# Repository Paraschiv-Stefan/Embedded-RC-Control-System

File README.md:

# Transmitter (Controller)

Custom handheld controller for wireless control of the RC vehicle.  
  
I took down a worn down Xbox one controller, reused any parts that I could and remade my own PCB that fits inside the controller case so i can have a similar feel to the racing games I used to play and enojoy.

---

##  Overview

This transmitter is built around a **custom 4-layer PCB**, this being my firts PCB design ever I find it easier to start with a 4 layers, but if I am to go back to designing I would only make it in 2 layers, the complexity of the PCB itself is too low to justify the 4 layers.

The goal of this controller was to transmitt data over a radio module HC-12 which works at 433Mhz, and is capable of transmitting at distances as far away as 1km

---

## Hardware Design

### Microcontroller

* **PIC16F15276**
  Handles input processing and communication with the receiver. Cheap and easy to programm being a chip supported in the MCC from MpLab X IDE with a lot of configurable pins.

---

### User Input

* **Dual Joysticks**
  Provides steering control and menu configuration on the receiver

* **Hall Effect Sensors (from Xbox One controller)**
  Used for **high-precision, contactless throttle control**, improving reliability and eliminating mechanical wear.

---

## 📐 Schematic

> The schematic is fairly simple, at the center of it being the microcontroller, and all the analog pins needed that go to the joysticks and hall effect sensors as well as the uart communication for the HC-12 module.
---

## PCB Design

* **4-layer PCB**
* Designed for:

  * Compact handheld form factor

---

## PCB Layers

### Layer 1

> The first layer is primarily concerned with power distribution, ensuring all components across the board receive their required supply voltages.

### Layer 2

> This layer is dominated by the ground plane, while also accommodating the analog signal traces associated with the joystick inputs.

### Layer 3

> Similarly to the second layer, this layer is largely devoted to the ground plane, reinforcing the overall grounding strategy of the board.
### Layer 4

> The final layer is comparatively sparse, carrying only the traces dedicated to UART communication — keeping this relatively noise-sensitive interface clean and uncluttered

---

## Firmware

The firmware is responsible for:

* Reading joystick and sensor inputs
* Processing control signals
* Transmitting data wirelessly to the receiver with the help of the HC-12 module

---

## Functionality

* Real-time throttle and steering control
* Smooth input response using Hall effect sensing
* Reliable wireless communication
* Response time can be improved

---

## Notes

* Designed specifically for RC applications
* Focus on precision and responsiveness
* Built using salvaged components (Xbox controller sensors)

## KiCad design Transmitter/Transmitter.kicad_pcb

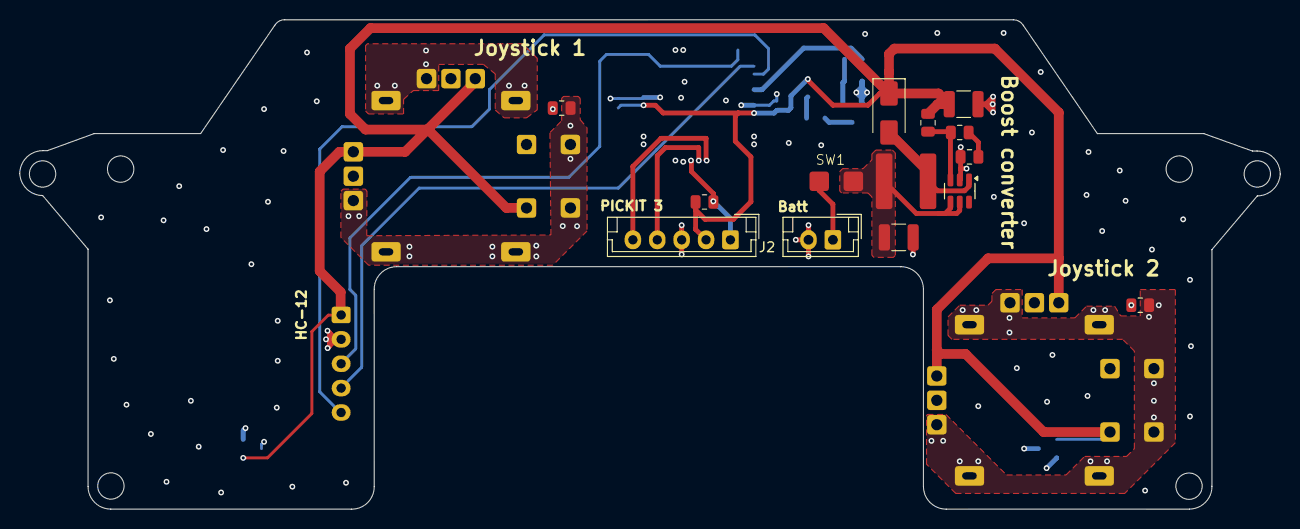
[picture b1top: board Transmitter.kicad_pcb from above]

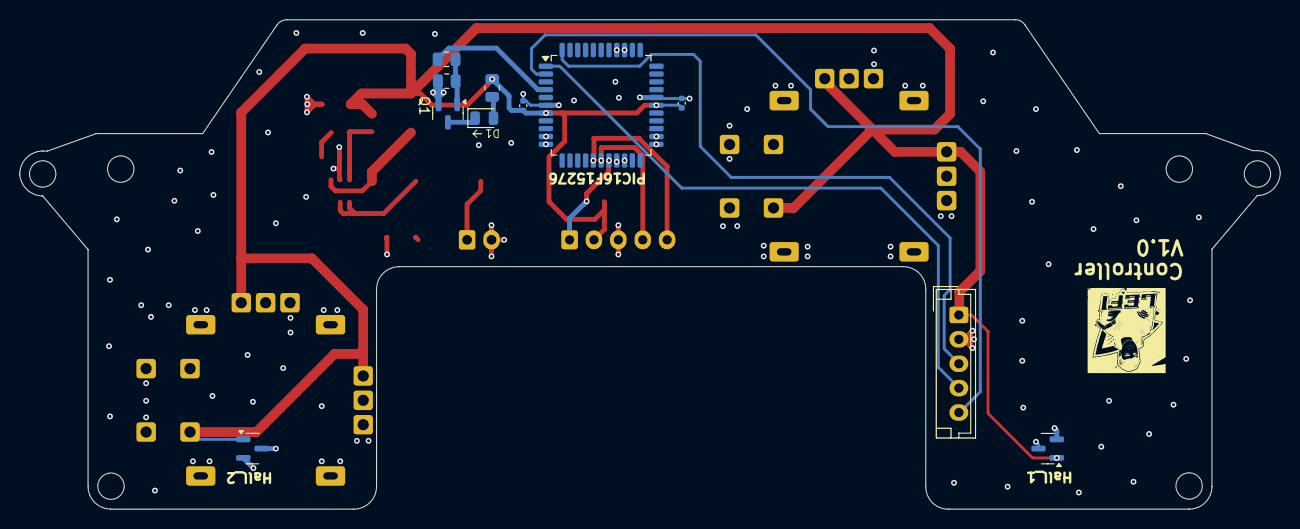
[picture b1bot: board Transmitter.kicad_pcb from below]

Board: 4 copper layers, 129.2 x 50.2 mm, 33 parts (11 on the bottom side), 25 nets.

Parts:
C1, C2: 100n; C_0402_1005Metric
C20, C21: 22u; C_1210_3225Metric
D1: LED; LED_0805_2012Metric
D20: SS14; D_SMA
H1, H2, H3, H4, H5, H6: MountingHole; MountingHole_2.7mm
J1, J4: Conn_01x05; JST_EH_B5B-EH-A_1x05_P2.50mm_Vertical
J2: Conn_01x02; JST_EH_B2B-EH-A_1x02_P2.50mm_Vertical
L20: 15u; inductor(mt3608)15u
Q1: BC817; SOT-23
R1, R22, R40, R41: 10k; R_0805_2012Metric
R20: 100; R_0805_2012Metric
R21, R31: 1k; R_0805_2012Metric
R30: 10.5k; R_0805_2012Metric
R32: 500; R_0805_2012Metric
SW1: SW_DIP_x01; Untitled
U1, U5: SOT-23
U2, U4: Joystick
U6: PIC18F4431-IPT; TQFP-44_10x10mm_P0.8mm
U20: MT3608; SOT-23-6

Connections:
/Hall_1: U1.2 (OUTPUT), U6.20 (RA1/AN1)
/Hall_2: U5.2 (OUTPUT), U6.19 (RA0/AN0)
/LED: R21.2, U6.4 (PWM6/RD6)
/MCLR: J4.1, R1.2, U6.18 (Vpp/~MCLR/RE3)
/PGC: J4.5, U6.16 (RB6/KBI2/PGC)
/PGD: J4.4, U6.17 (RB7/KBI3/PGD)
/RX: J1.4, U6.1 (RX/SDO/DT/RC7)
/SW1: R40.2, U2.3 (SW), U6.23 (RA4/AN4/CAP3/QEB)
/SW2: R41.2, U4.3 (SW), U6.24 (RA5/AN5/LVDIN)
/Set: J1.5, U6.2 (~FLTA/RD4)
/TX: J1.3, U6.44 (TX/~SS/CK/RC6)
/VBAT: C20.1, L20.1, SW1.2, U20.4 (EN), U20.5 (IN)
/VDD: C1.1, C2.1, C21.1, D20.1 (K), J1.1, J4.2, R1.1, R20.1, R30.1, U1.1 (VCC), U2.1 (VCC), U2.6 (SW), U4.1 (VCC), U4.6 (SW), U5.1 (VCC), U6.7 (VDD), U6.28 (AVDD)
/X1: U2.4 (Rx), U6.36 (~FLTB/CCP1/RC2)
/X2: U4.4 (Rx), U6.10 (RB2/PWM2)
/Y1: U2.5 (Ry), U6.37 (INT0/T5CKI/T0CKI/RC3)
/Y2: U4.5 (Ry), U6.11 (RB3/PWM3)
GND: C1.2, C2.2, C20.2, C21.2, J1.2, J2.2, J4.3, Q1.2 (E), R22.2, R32.2, R40.1, R41.1, U1.3 (GND), U2.0 (GND), U4.0 (GND), U5.3 (GND), U6.6 (VSS), U6.29 (AVSS), U20.2 (GND)
unnamed: D1.2 (A), R20.2
unnamed: D1.1 (K), Q1.3 (C)
unnamed: D20.2 (A), L20.2, U20.1 (SW)
unnamed: J2.1, SW1.1
unnamed: Q1.1 (B), R21.1, R22.1
unnamed: R31.2, R32.1
unnamed: R30.2, R31.1, U20.3 (FB)

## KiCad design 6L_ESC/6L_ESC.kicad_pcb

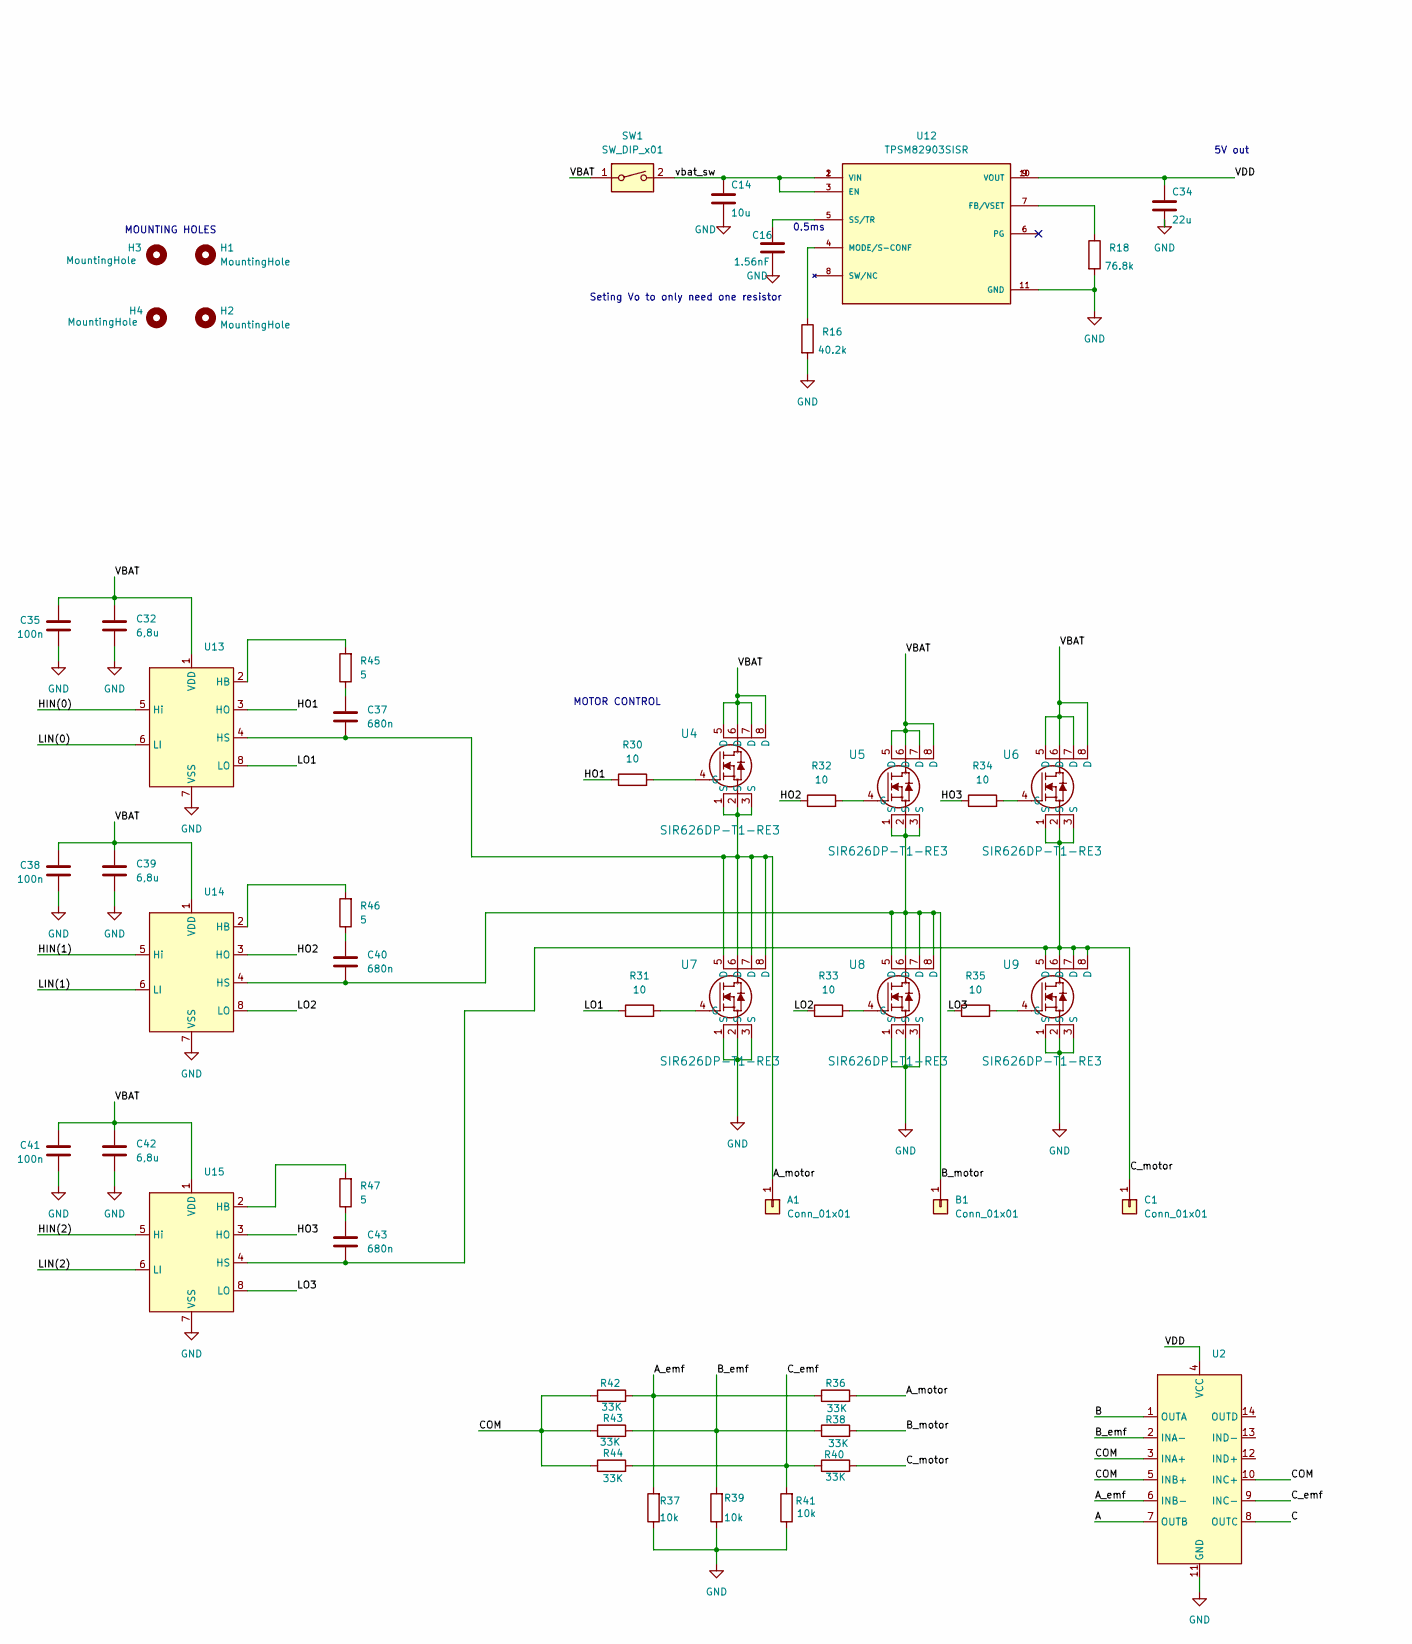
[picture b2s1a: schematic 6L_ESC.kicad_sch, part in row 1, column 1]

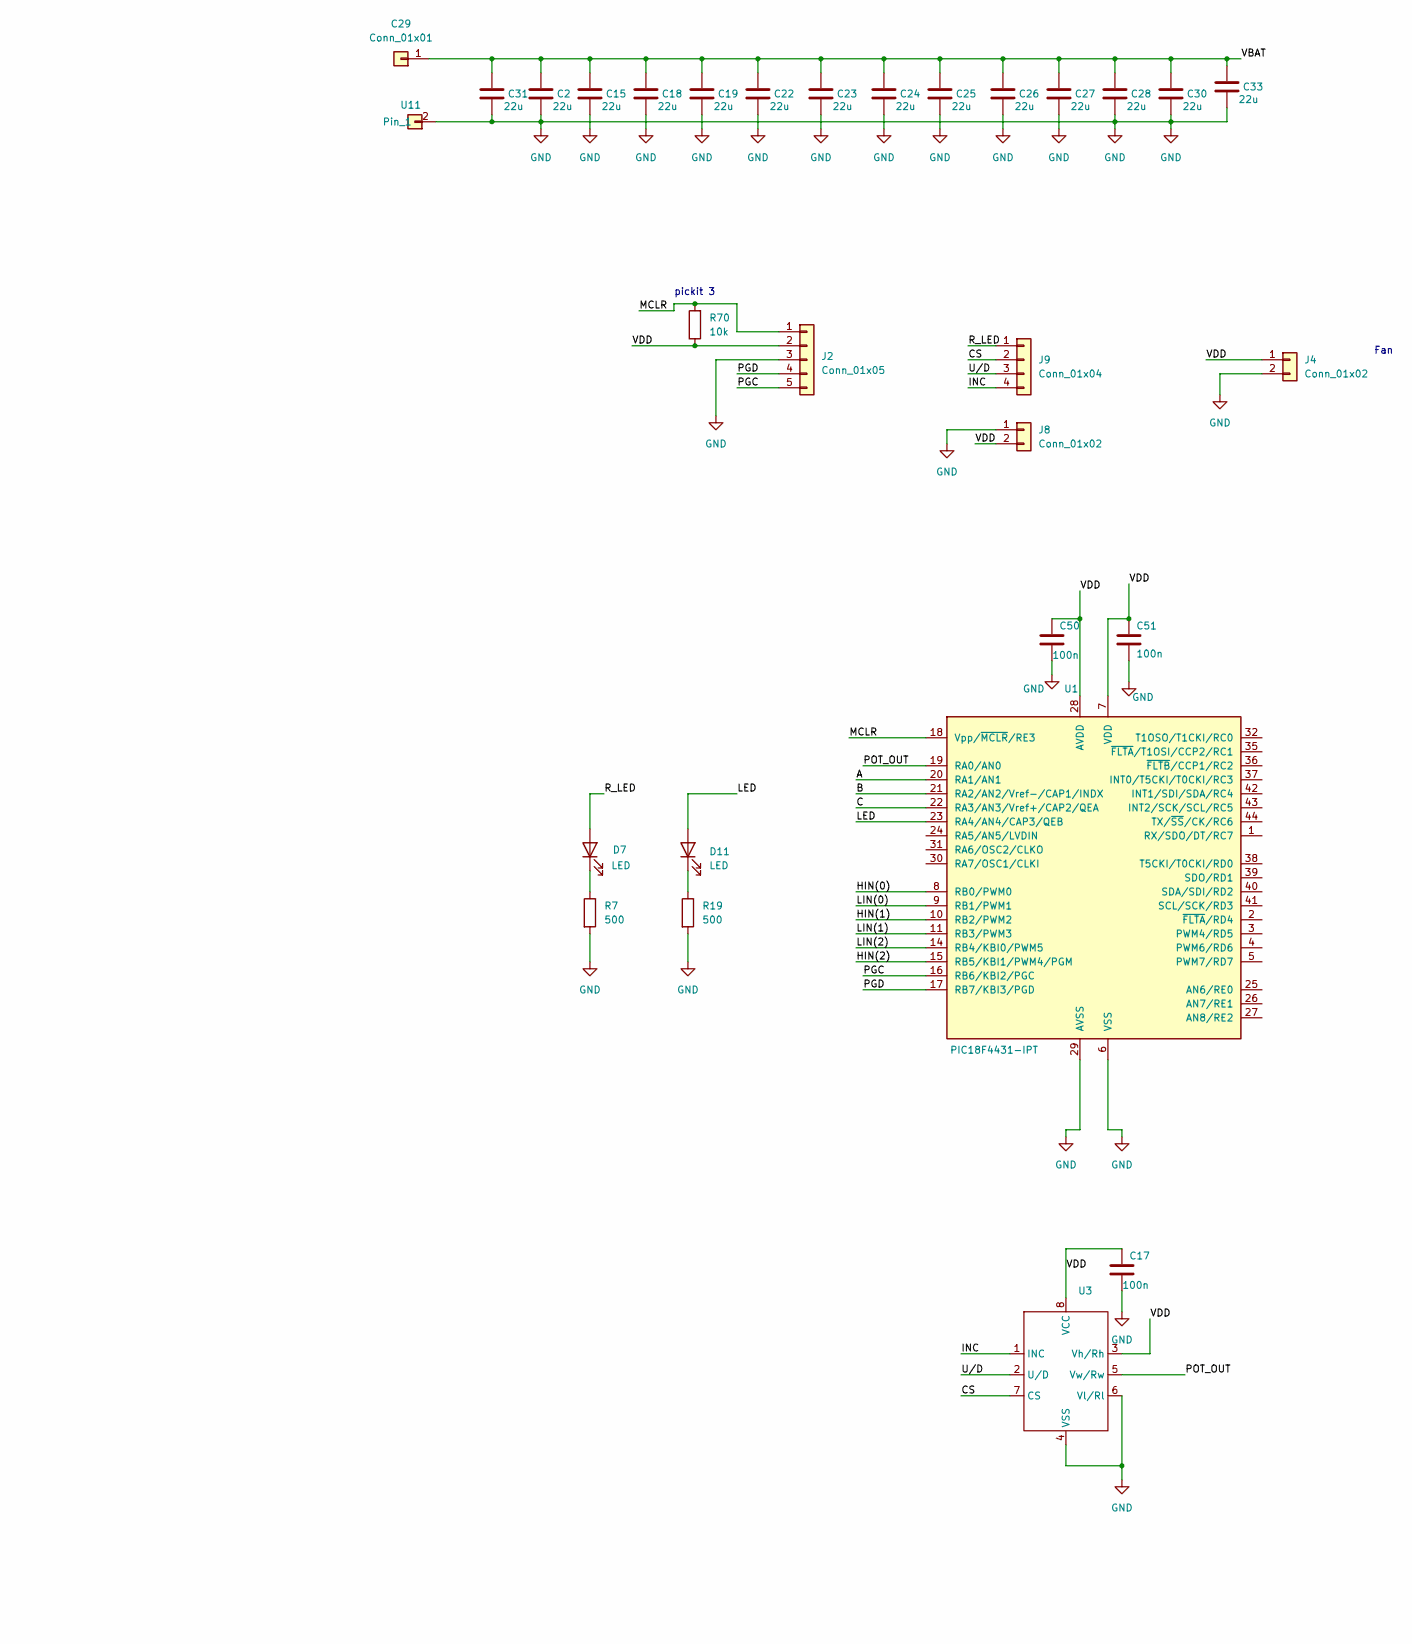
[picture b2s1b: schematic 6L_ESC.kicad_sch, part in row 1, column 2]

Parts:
A1: Conn_01x01; PHASE_PAD
B1: Conn_01x01; PHASE_PAD
C1: Conn_01x01; PHASE_PAD
C2, C15, C18, C19, C22, C23, C24, C25, C26, C27, C28, C30, C31, C33, C34: 22u; C_1210_3225Metric
C14: 10u; C_0805_2012Metric
C16: 1.56nF; C_0603_1608Metric
C17, C50, C51: 100n; C_0402_1005Metric
C29: Conn_01x01; BAT+
C32, C39, C42: 6,8u; C_0603_1608Metric
C35, C38, C41: 100n; C_0603_1608Metric
C37, C40, C43: 680n; C_0603_1608Metric
D7, D11: LED; LED_0805_2012Metric
H1, H2, H3, H4: MountingHole; MountingHole_2.1mm
J2: Conn_01x05; JST_EH_B5B-EH-A_1x05_P2.50mm_Vertical
J4: Conn_01x02; JST_EH_B2B-EH-A_1x02_P2.50mm_Vertical
J8: Conn_01x02; PinHeader_1x02_P2.54mm_Vertical
J9: Conn_01x04; PinHeader_1x04_P2.54mm_Vertical
R7, R19: 500; R_0805_2012Metric
R16: 40.2k; R_0603_1608Metric
R18: 76.8k; R_0603_1608Metric
R30, R31, R32, R33, R34, R35: 10; R_0805_2012Metric
R36, R38, R40, R42, R43, R44: 33K; R_0805_2012Metric
R37, R39, R41, R70: 10k; R_0805_2012Metric
R45, R46, R47: 5; R_1206_3216Metric
SW1: SW_DIP_x01; switch
U1: PIC18F4431-IPT; TQFP-44_10x10mm_P0.8mm
U2: comp_tssop-14_lm324
U3: SOIC-8_3.9x4.9mm_P1.27mm
U4, U5, U6: SIR626DP-T1-RE3; sir626_redefined
U7, U8, U9: SIR626DP-T1-RE3; sir626_les_holes
U11: BAT-
U12: TPSM82903SISR; IC_TPSM82903SISR; PARTREV B; DigiKey_Part_Number 296-TPSM82903SISRCT-ND
U13, U14, U15: NVC51511

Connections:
/A: U1.20 (RA1/AN1), U2.7 (OUTB)
/A_emf: R36.1, R37.2, R42.2, U2.6 (INB-)
/A_motor: A1.1, C37.2, R36.2, U4.1 (S), U4.2 (S), U4.3 (S), U7.5 (D), U7.6 (D), U7.7 (D), U7.8 (D), U13.4 (HS)
/B: U1.21 (RA2/AN2/Vref-/CAP1/INDX), U2.1 (OUTA)
/B_emf: R38.1, R39.2, R43.1, U2.2 (INA-)
/B_motor: B1.1, C40.2, R38.2, U5.1 (S), U5.2 (S), U5.3 (S), U8.5 (D), U8.6 (D), U8.7 (D), U8.8 (D), U14.4 (HS)
/C: U1.22 (RA3/AN3/Vref+/CAP2/QEA), U2.8 (OUTC)
/COM: R42.1, R43.2, R44.1, U2.3 (INA+), U2.5 (INB+), U2.10 (INC+)
/CS: J9.2, U3.7 (CS)
/C_emf: R40.1, R41.2, R44.2, U2.9 (INC-)
/C_motor: C1.1, C43.2, R40.2, U6.1 (S), U6.2 (S), U6.3 (S), U9.5 (D), U9.6 (D), U9.7 (D), U9.8 (D), U15.4 (HS)
/HIN(0): U1.8 (RB0/PWM0), U13.5 (Hi)
/HIN(1): U1.10 (RB2/PWM2), U14.5 (Hi)
/HIN(2): U1.15 (RB5/KBI1/PWM4/PGM), U15.5 (Hi)
/HO1: R30.1, U13.3 (HO)
/HO2: R32.1, U14.3 (HO)
/HO3: R34.1, U15.3 (HO)
/INC: J9.4, U3.1 (INC)
/LED: D11.2 (A), U1.23 (RA4/AN4/CAP3/QEB)
/LIN(0): U1.9 (RB1/PWM1), U13.6 (LI)
/LIN(1): U1.11 (RB3/PWM3), U14.6 (LI)
/LIN(2): U1.14 (RB4/KBI0/PWM5), U15.6 (LI)
/LO1: R31.1, U13.8 (LO)
/LO2: R33.1, U14.8 (LO)
/LO3: R35.1, U15.8 (LO)
/MCLR: J2.1, R70.2, U1.18 (Vpp/~MCLR/RE3)
/PGC: J2.5, U1.16 (RB6/KBI2/PGC)
/PGD: J2.4, U1.17 (RB7/KBI3/PGD)
/POT_OUT: U1.19 (RA0/AN0), U3.5 (Vw/Rw)
/R_LED: D7.2 (A), J9.1
/U/D: J9.3, U3.2 (U/D)
/VBAT: C2.1, C15.1, C18.1, C19.1, C22.1, C23.1, C24.1, C25.1, C26.1, C27.1, C28.1, C29.1, C30.1, C31.1, C32.1, C33.1, C35.1, C38.1, C39.1, C41.1, C42.1, SW1.1, U4.5 (D), U4.6 (D), U4.7 (D), U4.8 (D), U5.5 (D), U5.6 (D), U5.7 (D), U5.8 (D), U6.5 (D), U6.6 (D), U6.7 (D), U6.8 (D), U13.1 (VDD), U14.1 (VDD), U15.1 (VDD)
/VDD: C17.1, C34.1, C50.1, C51.1, J2.2, J4.1, J8.2, R70.1, U1.7 (VDD), U1.28 (AVDD), U2.4 (VCC), U3.3 (Vh/Rh), U3.8 (VCC), U12.9 (VOUT), U12.10 (VOUT)
/vbat_sw: C14.1, SW1.2, U12.1 (VIN), U12.2 (VIN), U12.3 (EN)
GND: C2.2, C14.2, C15.2, C16.2, C17.2, C18.2, C19.2, C22.2, C23.2, C24.2, C25.2, C26.2, C27.2, C28.2, C30.2, C31.2, C32.2, C33.2, C34.2, C35.2, C38.2, C39.2, C41.2, C42.2, C50.2, C51.2, J2.3, J4.2, J8.1, R7.2, R16.2, R18.2, R19.2, R37.1, R39.1, R41.1, U1.6 (VSS), U1.29 (AVSS), U2.11 (GND), U3.4 (VSS), U3.6 (Vl/Rl), U7.1 (S), U7.2 (S), U7.3 (S), U8.1 (S), U8.2 (S), U8.3 (S), U9.1 (S), U9.2 (S), U9.3 (S), U11.2 (Pin_1), U12.11 (GND), U13.7 (VSS), U14.7 (VSS), U15.7 (VSS)
unnamed: C37.1, R45.1
unnamed: C40.1, R46.1
unnamed: C43.1, R47.1
unnamed: D7.1 (K), R7.1
unnamed: D11.1 (K), R19.1
unnamed: R30.2, U4.4 (G)
unnamed: R32.2, U5.4 (G)
unnamed: R34.2, U6.4 (G)
unnamed: R31.2, U7.4 (G)
unnamed: R33.2, U8.4 (G)
unnamed: R35.2, U9.4 (G)
unnamed: R18.1, U12.7 (FB/VSET)
unnamed: R16.1, U12.4 (MODE/S-CONF)
unnamed: C16.1, U12.5 (SS/TR)
unnamed: R45.2, U13.2 (HB)
unnamed: R46.2, U14.2 (HB)
unnamed: R47.2, U15.2 (HB)

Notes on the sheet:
Seting Vo to only need one resistor
Fan
MOTOR CONTROL
MOUNTING HOLES
0.5ms
pickit 3
5V out

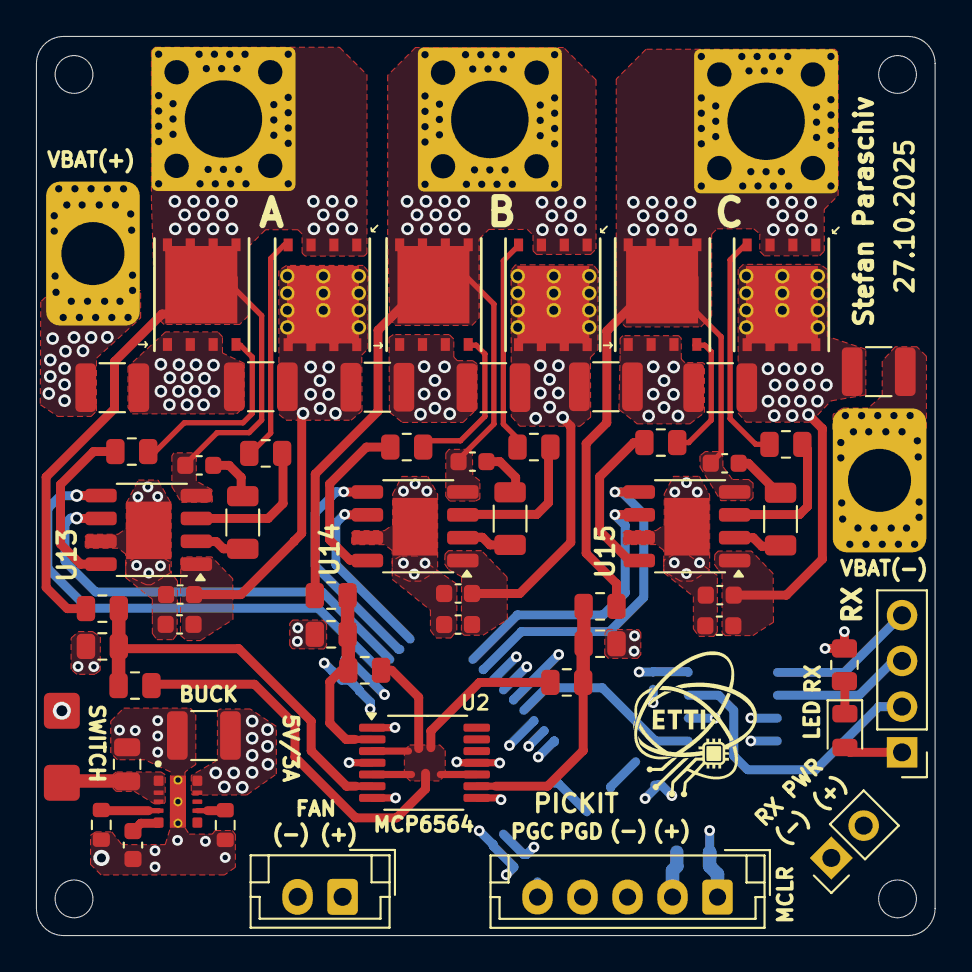
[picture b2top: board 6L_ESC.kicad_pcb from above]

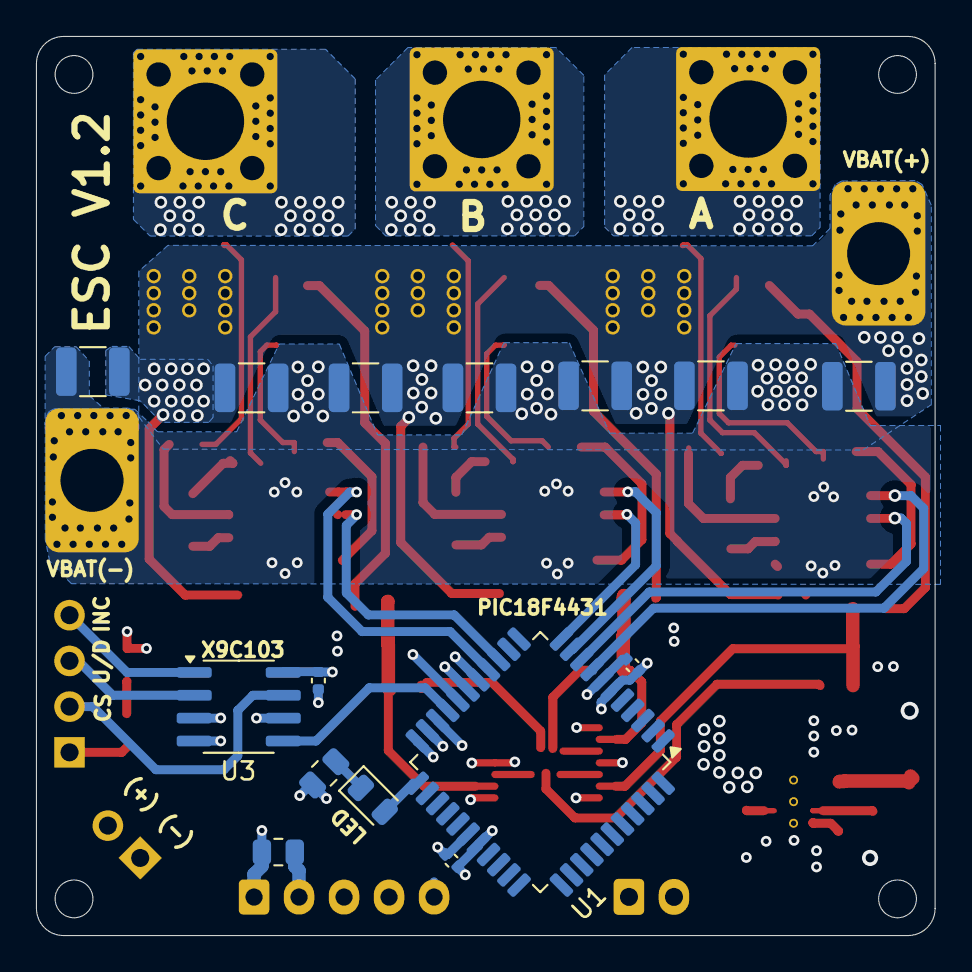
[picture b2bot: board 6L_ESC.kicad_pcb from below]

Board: 6 copper layers, 49.9 x 49.9 mm, 81 parts (15 on the bottom side), 52 nets.

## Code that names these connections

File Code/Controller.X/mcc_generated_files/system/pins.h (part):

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// get/set IO_RA0 aliases
#define IO_RA0_TRIS                 TRISAbits.TRISA0
#define IO_RA0_LAT                  LATAbits.LATA0
#define IO_RA0_PORT                 PORTAbits.RA0
#define IO_RA0_WPU                  WPUAbits.WPUA0
#define IO_RA0_OD                   ODCONAbits.ODCA0
#define IO_RA0_ANS                  ANSELAbits.ANSA0
#define IO_RA0_SetHigh()            do { LATAbits.LATA0 = 1; } while(0)
#define IO_RA0_SetLow()             do { LATAbits.LATA0 = 0; } while(0)
#define IO_RA0_Toggle()             do { LATAbits.LATA0 = ~LATAbits.LATA0; } while(0)
#define IO_RA0_GetValue()           PORTAbits.RA0
#define IO_RA0_SetDigitalInput()    do { TRISAbits.TRISA0 = 1; } while(0)
#define IO_RA0_SetDigitalOutput()   do { TRISAbits.TRISA0 = 0; } while(0)
#define IO_RA0_SetPullup()          do { WPUAbits.WPUA0 = 1; } while(0)
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// get/set IO_RA1 aliases
#define IO_RA1_TRIS                 TRISAbits.TRISA1
#define IO_RA1_LAT                  LATAbits.LATA1
#define IO_RA1_PORT                 PORTAbits.RA1
#define IO_RA1_WPU                  WPUAbits.WPUA1
#define IO_RA1_OD                   ODCONAbits.ODCA1
#define IO_RA1_ANS                  ANSELAbits.ANSA1
#define IO_RA1_SetHigh()            do { LATAbits.LATA1 = 1; } while(0)
#define IO_RA1_SetLow()             do { LATAbits.LATA1 = 0; } while(0)
#define IO_RA1_Toggle()             do { LATAbits.LATA1 = ~LATAbits.LATA1; } while(0)
#define IO_RA1_GetValue()           PORTAbits.RA1
#define IO_RA1_SetDigitalInput()    do { TRISAbits.TRISA1 = 1; } while(0)
#define IO_RA1_SetDigitalOutput()   do { TRISAbits.TRISA1 = 0; } while(0)
#define IO_RA1_SetPullup()          do { WPUAbits.WPUA1 = 1; } while(0)
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// get/set IO_RA2 aliases
#define IO_RA2_TRIS                 TRISAbits.TRISA2
#define IO_RA2_LAT                  LATAbits.LATA2
#define IO_RA2_PORT                 PORTAbits.RA2
#define IO_RA2_WPU                  WPUAbits.WPUA2
#define IO_RA2_OD                   ODCONAbits.ODCA2
#define IO_RA2_ANS                  ANSELAbits.ANSA2
#define IO_RA2_SetHigh()            do { LATAbits.LATA2 = 1; } while(0)
#define IO_RA2_SetLow()             do { LATAbits.LATA2 = 0; } while(0)
#define IO_RA2_Toggle()             do { LATAbits.LATA2 = ~LATAbits.LATA2; } while(0)
#define IO_RA2_GetValue()           PORTAbits.RA2
#define IO_RA2_SetDigitalInput()    do { TRISAbits.TRISA2 = 1; } while(0)
#define IO_RA2_SetDigitalOutput()   do { TRISAbits.TRISA2 = 0; } while(0)
#define IO_RA2_SetPullup()          do { WPUAbits.WPUA2 = 1; } while(0)
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// get/set IO_RA3 aliases
#define IO_RA3_TRIS                 TRISAbits.TRISA3
#define IO_RA3_LAT                  LATAbits.LATA3
#define IO_RA3_PORT                 PORTAbits.RA3
#define IO_RA3_WPU                  WPUAbits.WPUA3
#define IO_RA3_OD                   ODCONAbits.ODCA3
#define IO_RA3_ANS                  ANSELAbits.ANSA3
#define IO_RA3_SetHigh()            do { LATAbits.LATA3 = 1; } while(0)
#define IO_RA3_SetLow()             do { LATAbits.LATA3 = 0; } while(0)
#define IO_RA3_Toggle()             do { LATAbits.LATA3 = ~LATAbits.LATA3; } while(0)
#define IO_RA3_GetValue()           PORTAbits.RA3
#define IO_RA3_SetDigitalInput()    do { TRISAbits.TRISA3 = 1; } while(0)
#define IO_RA3_SetDigitalOutput()   do { TRISAbits.TRISA3 = 0; } while(0)
#define IO_RA3_SetPullup()          do { WPUAbits.WPUA3 = 1; } while(0)
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// get/set IO_RA5 aliases
#define IO_RA5_TRIS                 TRISAbits.TRISA5
#define IO_RA5_LAT                  LATAbits.LATA5
#define IO_RA5_PORT                 PORTAbits.RA5
#define IO_RA5_WPU                  WPUAbits.WPUA5
#define IO_RA5_OD                   ODCONAbits.ODCA5
#define IO_RA5_ANS                  ANSELAbits.ANSA5
#define IO_RA5_SetHigh()            do { LATAbits.LATA5 = 1; } while(0)
#define IO_RA5_SetLow()             do { LATAbits.LATA5 = 0; } while(0)
#define IO_RA5_Toggle()             do { LATAbits.LATA5 = ~LATAbits.LATA5; } while(0)
#define IO_RA5_GetValue()           PORTAbits.RA5
#define IO_RA5_SetDigitalInput()    do { TRISAbits.TRISA5 = 1; } while(0)
#define IO_RA5_SetDigitalOutput()   do { TRISAbits.TRISA5 = 0; } while(0)
#define IO_RA5_SetPullup()          do { WPUAbits.WPUA5 = 1; } while(0)
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// get/set IO_RB3 aliases
#define IO_RB3_TRIS                 TRISBbits.TRISB3
#define IO_RB3_LAT                  LATBbits.LATB3
#define IO_RB3_PORT                 PORTBbits.RB3
#define IO_RB3_WPU                  WPUBbits.WPUB3
#define IO_RB3_OD                   ODCONBbits.ODCB3
#define IO_RB3_ANS                  ANSELBbits.ANSB3
#define IO_RB3_SetHigh()            do { LATBbits.LATB3 = 1; } while(0)
#define IO_RB3_SetLow()             do { LATBbits.LATB3 = 0; } while(0)
#define IO_RB3_Toggle()             do { LATBbits.LATB3 = ~LATBbits.LATB3; } while(0)
#define IO_RB3_GetValue()           PORTBbits.RB3
#define IO_RB3_SetDigitalInput()    do { TRISBbits.TRISB3 = 1; } while(0)
#define IO_RB3_SetDigitalOutput()   do { TRISBbits.TRISB3 = 0; } while(0)
#define IO_RB3_SetPullup()          do { WPUBbits.WPUB3 = 1; } while(0)
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// get/set IO_RC6 aliases
#define IO_RC6_TRIS                 TRISCbits.TRISC6
#define IO_RC6_LAT                  LATCbits.LATC6
#define IO_RC6_PORT                 PORTCbits.RC6
#define IO_RC6_WPU                  WPUCbits.WPUC6
#define IO_RC6_OD                   ODCONCbits.ODCC6
#define IO_RC6_ANS                  ANSELCbits.ANSC6
#define IO_RC6_SetHigh()            do { LATCbits.LATC6 = 1; } while(0)
#define IO_RC6_SetLow()             do { LATCbits.LATC6 = 0; } while(0)
#define IO_RC6_Toggle()             do { LATCbits.LATC6 = ~LATCbits.LATC6; } while(0)
#define IO_RC6_GetValue()           PORTCbits.RC6
#define IO_RC6_SetDigitalInput()    do { TRISCbits.TRISC6 = 1; } while(0)
#define IO_RC6_SetDigitalOutput()   do { TRISCbits.TRISC6 = 0; } while(0)
#define IO_RC6_SetPullup()          do { WPUCbits.WPUC6 = 1; } while(0)
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// get/set IO_RC7 aliases
#define IO_RC7_TRIS                 TRISCbits.TRISC7
#define IO_RC7_LAT                  LATCbits.LATC7
#define IO_RC7_PORT                 PORTCbits.RC7
#define IO_RC7_WPU                  WPUCbits.WPUC7
#define IO_RC7_OD                   ODCONCbits.ODCC7
#define IO_RC7_ANS                  ANSELCbits.ANSC7
#define IO_RC7_SetHigh()            do { LATCbits.LATC7 = 1; } while(0)
#define IO_RC7_SetLow()             do { LATCbits.LATC7 = 0; } while(0)
#define IO_RC7_Toggle()             do { LATCbits.LATC7 = ~LATCbits.LATC7; } while(0)
#define IO_RC7_GetValue()           PORTCbits.RC7
#define IO_RC7_SetDigitalInput()    do { TRISCbits.TRISC7 = 1; } while(0)
#define IO_RC7_SetDigitalOutput()   do { TRISCbits.TRISC7 = 0; } while(0)
#define IO_RC7_SetPullup()          do { WPUCbits.WPUC7 = 1; } while(0)
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// get/set IO_RD6 aliases
#define IO_RD6_TRIS                 TRISDbits.TRISD6
#define IO_RD6_LAT                  LATDbits.LATD6
#define IO_RD6_PORT                 PORTDbits.RD6
#define IO_RD6_WPU                  WPUDbits.WPUD6
#define IO_RD6_OD                   ODCONDbits.ODCD6
#define IO_RD6_ANS                  ANSELDbits.ANSD6
#define IO_RD6_SetHigh()            do { LATDbits.LATD6 = 1; } while(0)
#define IO_RD6_SetLow()             do { LATDbits.LATD6 = 0; } while(0)
#define IO_RD6_Toggle()             do { LATDbits.LATD6 = ~LATDbits.LATD6; } while(0)
#define IO_RD6_GetValue()           PORTDbits.RD6
#define IO_RD6_SetDigitalInput()    do { TRISDbits.TRISD6 = 1; } while(0)
#define IO_RD6_SetDigitalOutput()   do { TRISDbits.TRISD6 = 0; } while(0)
#define IO_RD6_SetPullup()          do { WPUDbits.WPUD6 = 1; } while(0)
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

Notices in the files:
Code/Controller.X/mcc_generated_files/system/pins.h:
© [2025] Microchip Technology Inc. and its subsidiaries.
